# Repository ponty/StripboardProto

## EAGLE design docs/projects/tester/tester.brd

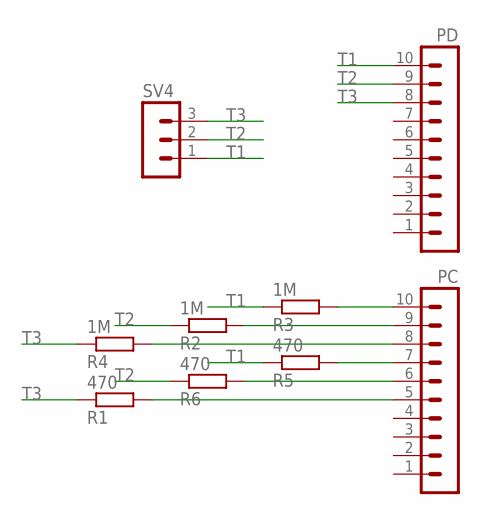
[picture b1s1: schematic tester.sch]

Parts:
PC: MA10-1W
PD: MA10-1W
R1, R5, R6: 470; R1206
R2, R3, R4: 1M; R1206
SV4: MA03-1

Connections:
unnamed: PC.10, R3.2
unnamed: PC.9, R2.2
unnamed: PC.8, R4.2
unnamed: PC.7, R5.2
unnamed: PC.6, R6.2
unnamed: PC.5, R1.2
T1: PD.10, R3.1, R5.1, SV4.1
T2: PD.9, R2.1, R6.1, SV4.2
T3: PD.8, R1.1, R4.1, SV4.3

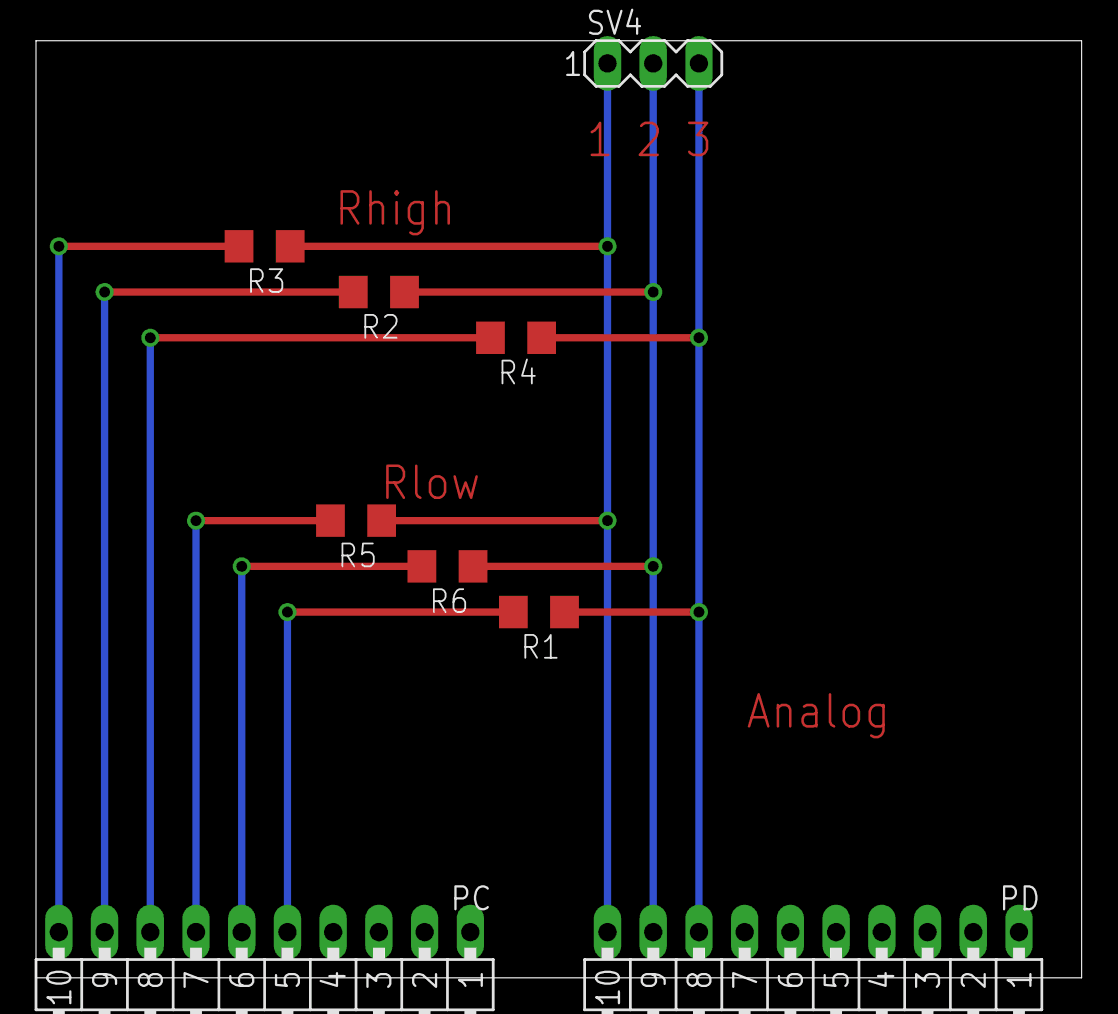
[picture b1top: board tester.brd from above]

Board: 2 copper layers, 58.1 x 52.1 mm, 9 parts (0 on the bottom side), 9 nets.

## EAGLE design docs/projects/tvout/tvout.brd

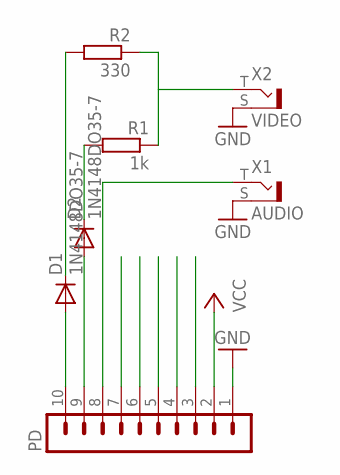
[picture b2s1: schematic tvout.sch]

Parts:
D1, D2: 1N4148DO35-7; DO35-7
PD: MA10-1W
R1: 1k; 0207/10
R2: 330; 0207/12
X1: AUDIO; WBTOR1
X2: VIDEO; WBTOR1

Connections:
unnamed: D1.C, R2.2
unnamed: D1.A, PD.10
unnamed: D2.A, PD.9
unnamed: D2.C, R1.2
unnamed: R1.1, R2.1, X2.T
unnamed: PD.1, X1.S, X2.S
unnamed: PD.8, X1.T
VCC: PD.2

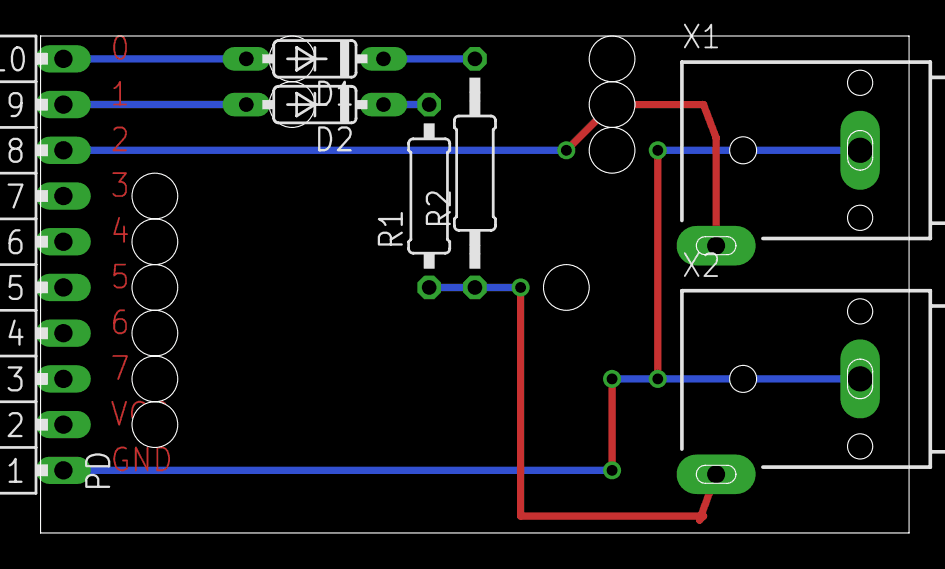
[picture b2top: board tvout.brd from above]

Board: 2 copper layers, 48.2 x 27.6 mm, 7 parts (0 on the bottom side), 7 nets.

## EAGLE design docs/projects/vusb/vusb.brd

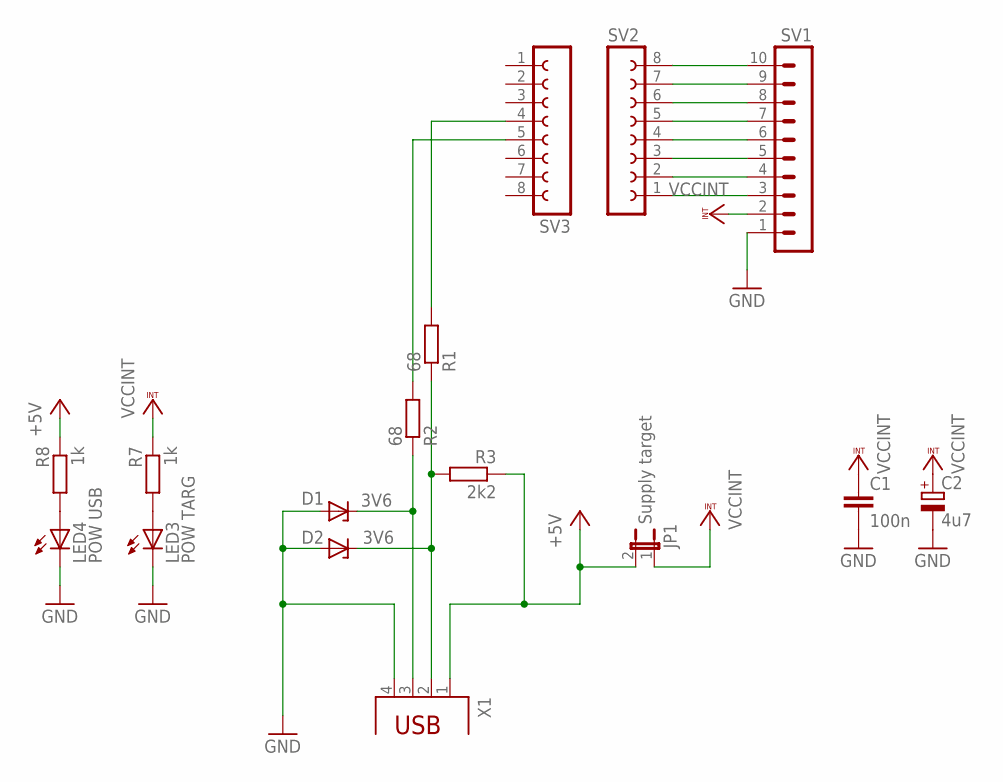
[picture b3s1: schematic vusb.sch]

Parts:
C1: 100n; C025-024X044
C2: 4u7; TT2D5
D1: 3V6; DO34Z7
D2: 3V6; ZDIO-5
JP1: Supply target; JP1
LED3: POW TARG; LED3MM
LED4: POW USB; LED3MM
R1, R2: 68; 0207/10
R3: 2k2; 0204V
R7, R8: 1k; 0207/10
SV1: MA10-1W
SV2, SV3: FE08-1; FE08
X1: PN61729

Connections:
GND: C1.2, C2.-, D1.A, D2.A, LED3.K (C), LED4.K (C), SV1.1, X1.4
unnamed: LED3.A, R7.2
unnamed: D1.C, R2.1, X1.3
unnamed: JP1.2, R3.1, R8.1, X1.1
unnamed: LED4.A, R8.2
unnamed: D2.C, R1.1, R3.2, X1.2
unnamed: SV1.3, SV2.1
unnamed: R1.2, SV3.4
unnamed: SV1.4, SV2.2
unnamed: SV1.5, SV2.3
unnamed: SV1.6, SV2.4
unnamed: SV1.7, SV2.5
unnamed: SV1.8, SV2.6
unnamed: SV1.9, SV2.7
unnamed: SV1.10, SV2.8
unnamed: R2.2, SV3.5
VCCINT: C1.1, C2.+, JP1.1, R7.1, SV1.2

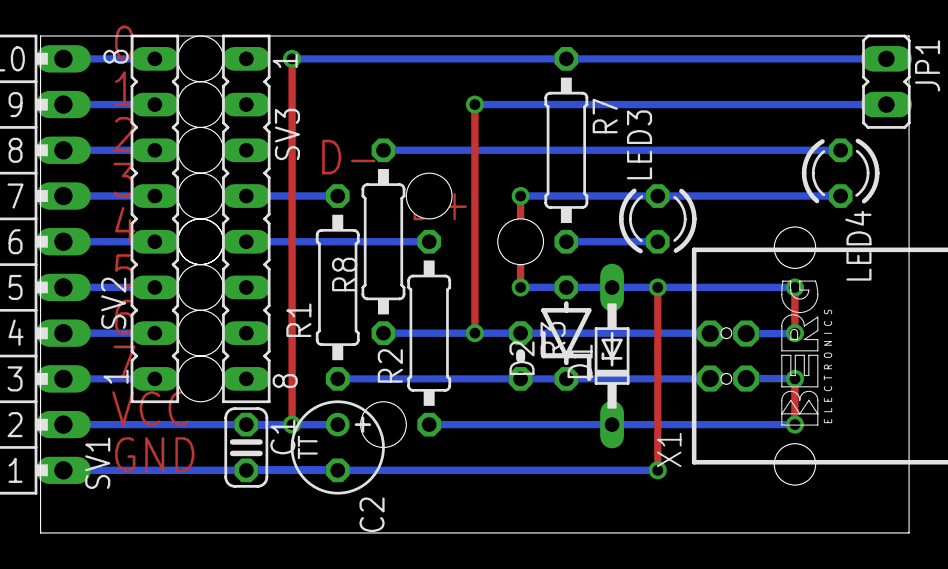
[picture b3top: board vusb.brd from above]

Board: 2 copper layers, 48.2 x 27.6 mm, 16 parts (0 on the bottom side), 17 nets.
